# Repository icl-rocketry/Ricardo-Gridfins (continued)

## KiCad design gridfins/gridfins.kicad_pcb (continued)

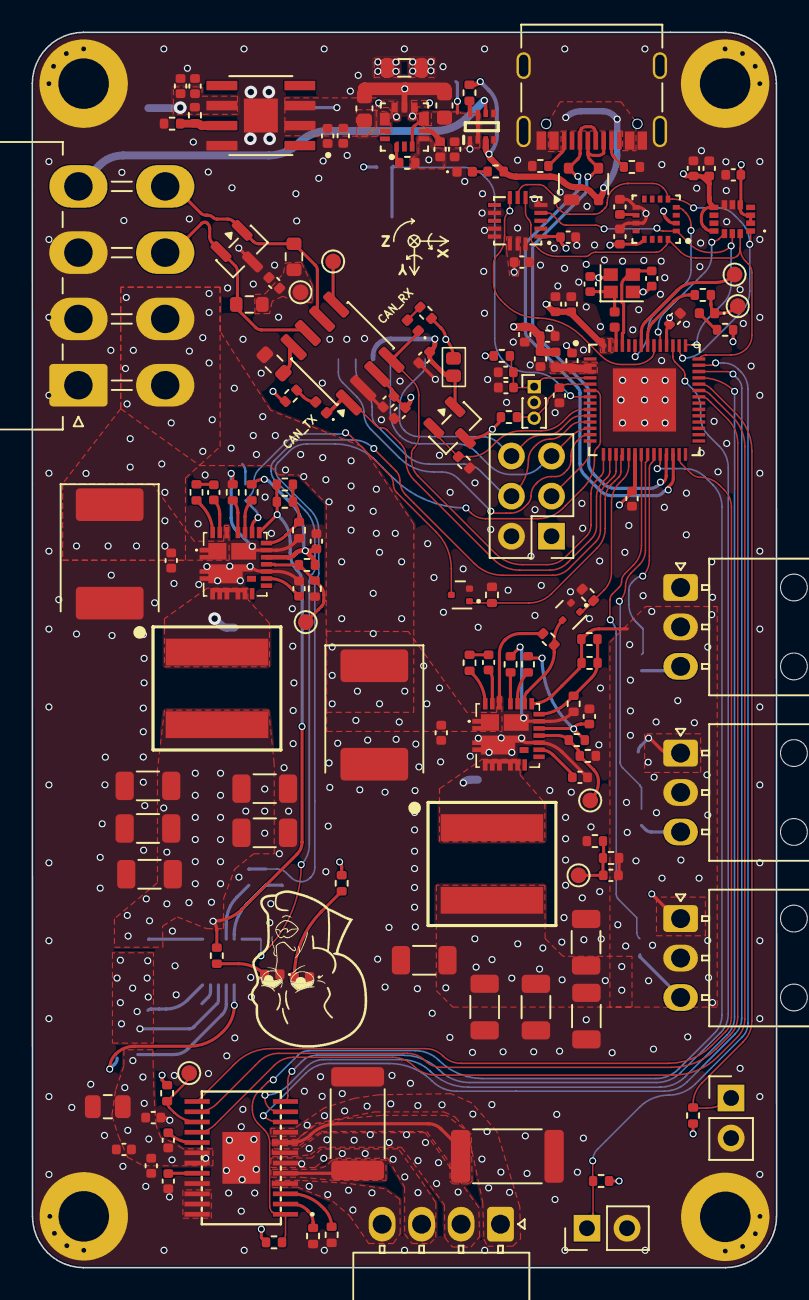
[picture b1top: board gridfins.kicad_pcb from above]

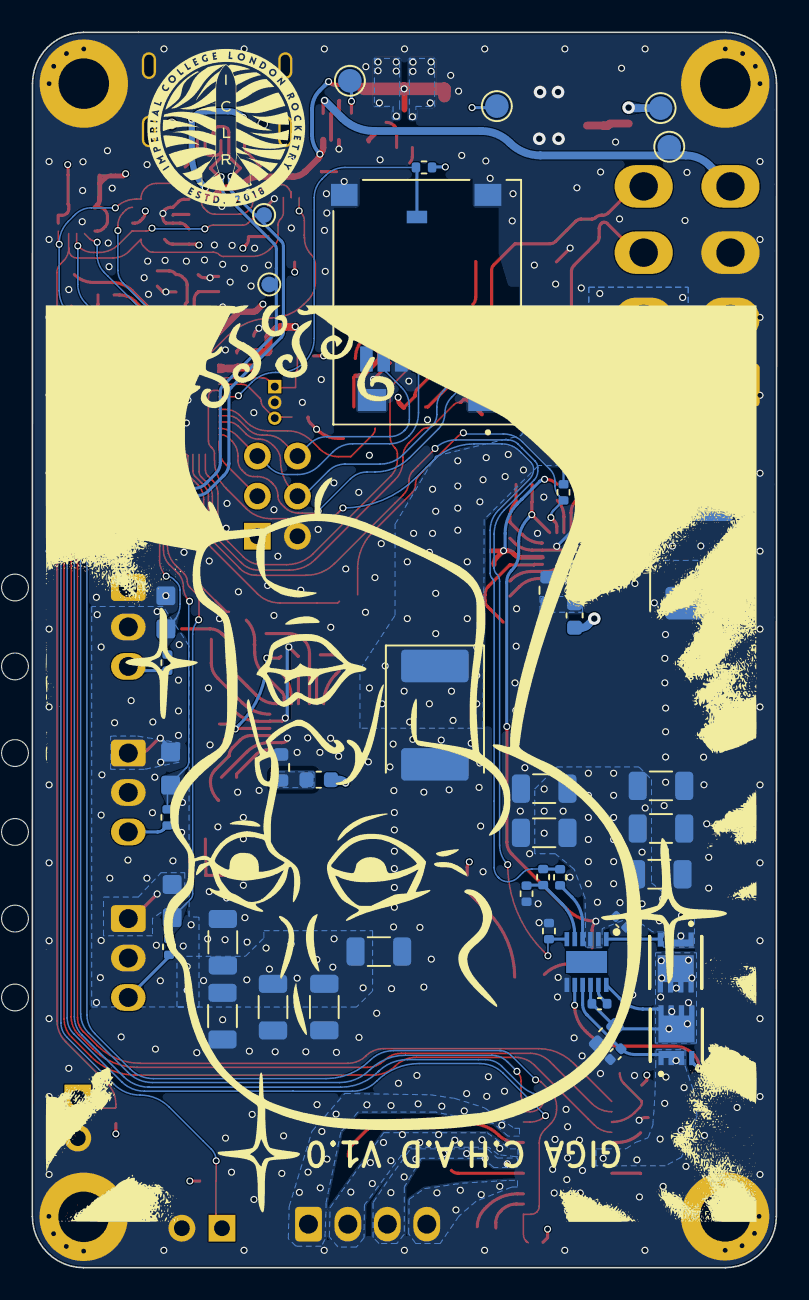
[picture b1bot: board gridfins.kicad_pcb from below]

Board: 4 copper layers, 47.2 x 78.3 mm, 202 parts (43 on the bottom side), 119 nets.

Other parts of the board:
G**: orientation_marker
LOGO1: ICLR LOGO; iclr_logo_estd2018_10mm

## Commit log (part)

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2026-02-03 Initial board setup
    Made an LED. Copied Ricardo-Chad buck converters and servo pwm (and tvs diode)
    - added a third servo and parallel tvs diode circuit
    - sheet references/labels not fully updated yet
2026-02-03 update 2
    Renamed repeated resistor names. Changed typo in buck - removing the 442k resistor actually changes Vout to 7.4V not 8.4! We need 7.4V for servos.
2026-02-03 update 3
    added tvs diode chip module for 3rd servo
    added net connection to actuators sheet
    changed 6 to 7.4 label
2026-02-07 Update with Inertial Measurement Unit
    cloned IMU from pickle rick.
2026-02-07 forgot to save the file
2026-02-10 SD card, linear actuator encoders
    Imported microSD reader from Stark
    Added pin connectors and SPI routes for AS5048 magnetic rotary encoder to be used with the linear actuator/brushed motor
    Added test pads for SD reader and encoder chip select
2026-02-14 Deployment Power Cut Mechanism
    Employed the master high-side switch from flintandsteel to disable servo and linear actuator power once lower altitude limit reached. This will prevent electrical problems during touchdown:
    Routed power rail 16.8V to switch input. Switch output routed to buck input. When high-side switch is enabled, buck input voltage is pulled down, depowering the servos and linear actuator.
2026-02-24 deleted obsolete ICM-20608-G from IMU, added WSEN-ISDS adviced by Jack, a 6 axis IMU. Added footprint and symbol. Yet to finish connections and finish the "application circuit". Added footprint for 6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
2026-03-03 IMU replacement
    created symbol and completed operational circuit for the WSEN-IDS 6 axis imu chip. Chip select accessed through the same - IMU1_CS. Need to verify direction of SCL port
2026-03-03 Imported Official footprints and symbol
2026-03-07 PCB design
    Started drawing fill-out zones and organising the recommended PCB layout for the SiC437, 438 on the buck converter
2026-05-16 buck PCB
    progress - starting from buck converter STEP 4
    - Rboot ad Cboot placed near the chip and between pin 23 and 24. Both capcitor and resistor of the recommended size 0402
    moved snubber up to top layer
    began to move
    analog components to left side while power components to right of IC
2026-05-20 First Attempt connection of stepper motor driver for linear actuator
    Added connections of driver and 4 pin nano. Added hierarchical labels and connected to GPIO. Current configuration is the INDEX mode
2026-05-23 Power distribution rework
    Added missing main power supply voltage to Stepper Motor Driver Board
    Separate Buck converter for servo and linear actuator(stepper motor)
    16.8V -> Buck -> high side switch -> H-bridge -> 10V
    16.8V -> Buck -> Servo -> 7.4V
2026-06-06 PCB + schematic updates
    Solved footprint error which prevented PCB from updating
    Deleted old buck converter PCB design (old buck now replaced with 2 for servo and linear acc)
    Moved Snubber and crossed out capacitor network to the backside of board
    Unsure whether if the +10V routing is valid - currently connected via tracers, not planes (may be a problem for current)
    Restructured old pcb which previously had planes associated with no nets (assigned nets to them)
    If current design approved, will proceed to carry out the same design for the servo controlling buck converter.
2026-06-26 Handoff
    implemented changes advised by Will. Still a bit unsure about how the EPAD should be connected to ground. The PCB design of both buck converters for servo and Hbridge(linear accuator) was completed -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
